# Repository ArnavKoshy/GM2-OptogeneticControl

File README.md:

# GM2-OptogeneticControl
A repository holding information and resources about the GM2 project about optogenetic control in bioreactors for enzyme synthesis

For information about the project, what we've done and how it relates to UN Sustainable Development Goals, see [About](About/)

For information about the testing rig used to collect light intensity data around a bioreactor, see [Testing Rig](Testing%20Rig/)

For information about our light distribution model, see [Modelling](Modelling/)

For information about the final lighting rig design to light a bioreactor, see [Lighting Rig](Lighting%20Rig/)

**For Alexandre**: A list of handover documentation we've each individually contributed to is available in [Individual handover notes](Individual%20Handover%20Notes.md)

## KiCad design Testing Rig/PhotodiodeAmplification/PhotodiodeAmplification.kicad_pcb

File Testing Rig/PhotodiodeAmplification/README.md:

Description of circuitry, instructions for assembly/modifications

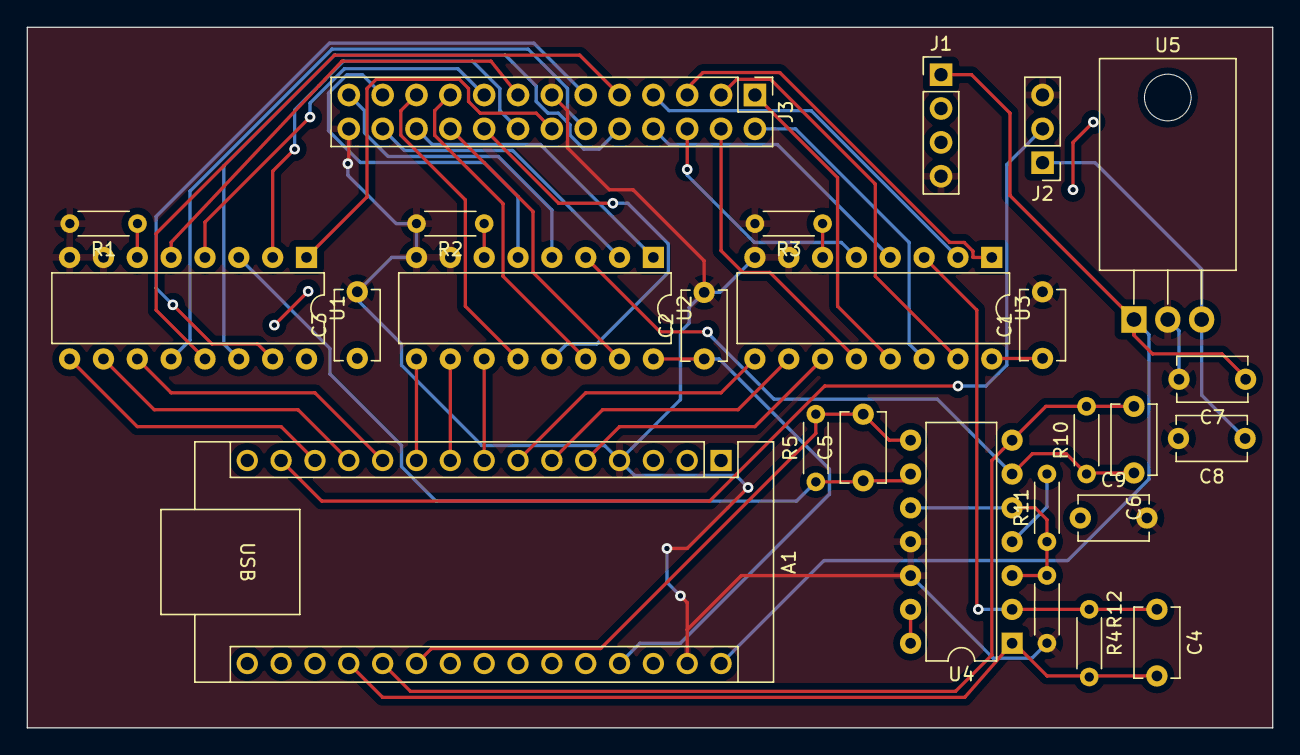
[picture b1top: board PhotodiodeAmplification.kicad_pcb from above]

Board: 2 copper layers, 93.5 x 52.6 mm, 26 parts (0 on the bottom side), 49 nets.

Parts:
A1: Arduino_Nano_Every; Arduino_Nano
C1, C2, C3, C8, C9: 0.1u; C_Disc_D5.1mm_W3.2mm_P5.00mm
C4, C5, C6: 20pF; C_Disc_D5.1mm_W3.2mm_P5.00mm
C7: 0.33u; C_Disc_D5.1mm_W3.2mm_P5.00mm
J1: Conn_01x04_Pin; PinHeader_1x04_P2.54mm_Vertical
J2: Conn_01x03_Pin; PinHeader_1x03_P2.54mm_Vertical
J3: Conn_02x13_Top_Bottom; PinHeader_2x13_P2.54mm_Vertical
R1, R2, R3, R12: 10k; R_Axial_DIN0204_L3.6mm_D1.6mm_P5.08mm_Horizontal
R4, R5, R10: 100k; R_Axial_DIN0204_L3.6mm_D1.6mm_P5.08mm_Horizontal
R11: 1M; R_Axial_DIN0204_L3.6mm_D1.6mm_P5.08mm_Horizontal
U1, U2, U3: 74HCT4051; DIP-16_W7.62mm
U4: MCP6004; DIP-14_W7.62mm
U5: L7805; TO-220-3_Horizontal_TabDown

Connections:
+5V: A1.27 (+5V), C1.1, C2.1, C3.1, C9.1, R11.2, U1.16 (VCC), U2.16 (VCC), U3.16 (VCC), U4.4 (V+)
+5VP: C8.1, J2.1, U5.3 (OUT)
+12V: A1.30 (VIN), C7.1, J1.1, U5.1 (IN)
/Amp/Mux1SelA: A1.5 (D2), U3.11 (S0)
/Amp/Mux1SelB: A1.6 (D3), U3.10 (S1)
/Amp/Mux1SelC: A1.7 (D4), U3.9 (S2)
/Amp/Mux2SelA: A1.8 (D5), U2.11 (S0)
/Amp/Mux2SelB: A1.9 (D6), U2.10 (S1)
/Amp/Mux2SelC: A1.10 (D7), U2.9 (S2)
/Amp/Mux3SelA: A1.11 (D8), U1.11 (S0)
/Amp/Mux3SelB: A1.12 (D9), U1.10 (S1)
/Amp/Mux3SelC: A1.13 (D10), U1.9 (S2)
/Amp/PhotodiodesMuxed1/Out: C4.1, R4.1, U3.3 (A), U4.2 (-)
/Amp/PhotodiodesMuxed2/Out: C5.1, R5.1, U1.3 (A), U4.9 (-)
/Amp/PhotodiodesMuxed3/Out: C6.1, R10.1, U2.3 (A), U4.6 (-)
/Amp/Vref: R11.1, R12.2, U4.3 (+), U4.5 (+), U4.10 (+)
/LED_Data: A1.14 (MOSI), J2.2
/Out1: A1.19 (A0), C4.2, R4.2, U4.1
/Out2: A1.20 (A1), C6.2, R10.2, U4.7
/Out3: A1.21 (A2), C5.2, R5.2, U4.8
GND: A1.4 (GND), A1.29 (GND), C1.2, C2.2, C3.2, C7.2, C8.2, C9.2, J1.4, J2.3, J3.13, J3.26, R1.2, R2.2, R3.2, R12.1, U1.7 (VEE), U1.8 (GND), U2.7 (VEE), U2.8 (GND), U3.7 (VEE), U3.8 (GND), U4.11 (V-), U4.12 (+), U5.2 (GND)
unnamed: R1.1, U1.6 (~E)
unnamed: R2.1, U2.6 (~E)
unnamed: R3.1, U3.6 (~E)
unnamed: U4.13 (-), U4.14
PD1: J3.1, U3.13 (A0)
PD2: J3.2, U3.14 (A1)
PD3: J3.3, U3.15 (A2)
PD4: J3.4, U3.12 (A3)
PD5: J3.5, U3.1 (A4)
PD6: J3.6, U3.5 (A5)
PD7: J3.7, U3.2 (A6)
PD8: J3.8, U3.4 (A7)
PD9: J3.9, U1.13 (A0)
PD10: J3.10, U1.14 (A1)
PD11: J3.11, U1.15 (A2)
PD12: J3.12, U1.12 (A3)
PD13: J3.14, U1.1 (A4)
PD14: J3.15, U1.5 (A5)
PD15: J3.16, U1.2 (A6)
PD16: J3.17, U1.4 (A7)
PD17: J3.18, U2.13 (A0)
PD18: J3.19, U2.14 (A1)
PD19: J3.20, U2.15 (A2)
PD20: J3.21, U2.12 (A3)
PD21: J3.22, U2.1 (A4)
PD22: J3.23, U2.5 (A5)
PD23: J3.24, U2.2 (A6)
PD24: J3.25, U2.4 (A7)

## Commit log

2023-06-03 Initial commit - collating everything
2023-06-04 Changed dir structure
2023-06-04 Retried dir structure
2023-06-05 Data processing
2023-06-05 DataAnalysis
2023-06-05 Updated main with interp and plotting
2023-06-06 design files for lighting rig
2023-06-06 design files for testing rig
2023-06-07 Clean up modelling section and document
2023-06-07 Update data collection
2023-06-07 Cleaned up data collection and updated docs
2023-06-07 Create temp
2023-06-07 specifying image size in README
2023-06-07 Added About files
2023-06-07 Added skeletons for about files
2023-06-07 Move components around
2023-06-08 Document circuit design and sims
2023-06-08 Renamed folder
2023-06-08 Update notes to reflect renaming
2023-06-08 Update project management
2023-06-08 Clarified some SDG wording
2023-06-08 Renamed file
